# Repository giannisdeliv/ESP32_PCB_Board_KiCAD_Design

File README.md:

# ESP32-C3 Sensor Board

It has been designed in KiCad as part of the Udemy course *Advanced PCB Design with KiCad 9*.(udemy.com/course/advanced-pcb-design-with-kicad/)

The design follows the course. 
I did the schematic capture, layout, and fabrication outputs.

## Features

- **MCU:** ESP32-C3-WROOM-02 (Wi-Fi / BLE), external 32 Mbit SPI flash (W25Q32JV)
- **USB:** USB-C, CP2102N USB-UART bridge, USBLC6-2SC6 ESD protection, resettable fuse
- **Power:** MCP73871 Li-Po charger with power-path management, LM1117 3.3 V LDO, JST-PH battery connector
- **Sensors:** BME280 (temperature / humidity / pressure), TEMT6000 ambient light, electret microphone with MAX4466 amplifier
- **Storage / UI:** microSD slot, status LEDs, Boot and Reset buttons
- **Debug:** test points on the SPI bus, pin headers for expansion

The custom footprint library "ESP32_Project_Footprints" and its 3D models were provided by the course and are not redistributed here. 
The footprints are embedded in "Demo.kicad_pcb", so the layout opens. 
Updating the PCB from the schematic requires the original library.

(Design only, not fabricated or tested.)

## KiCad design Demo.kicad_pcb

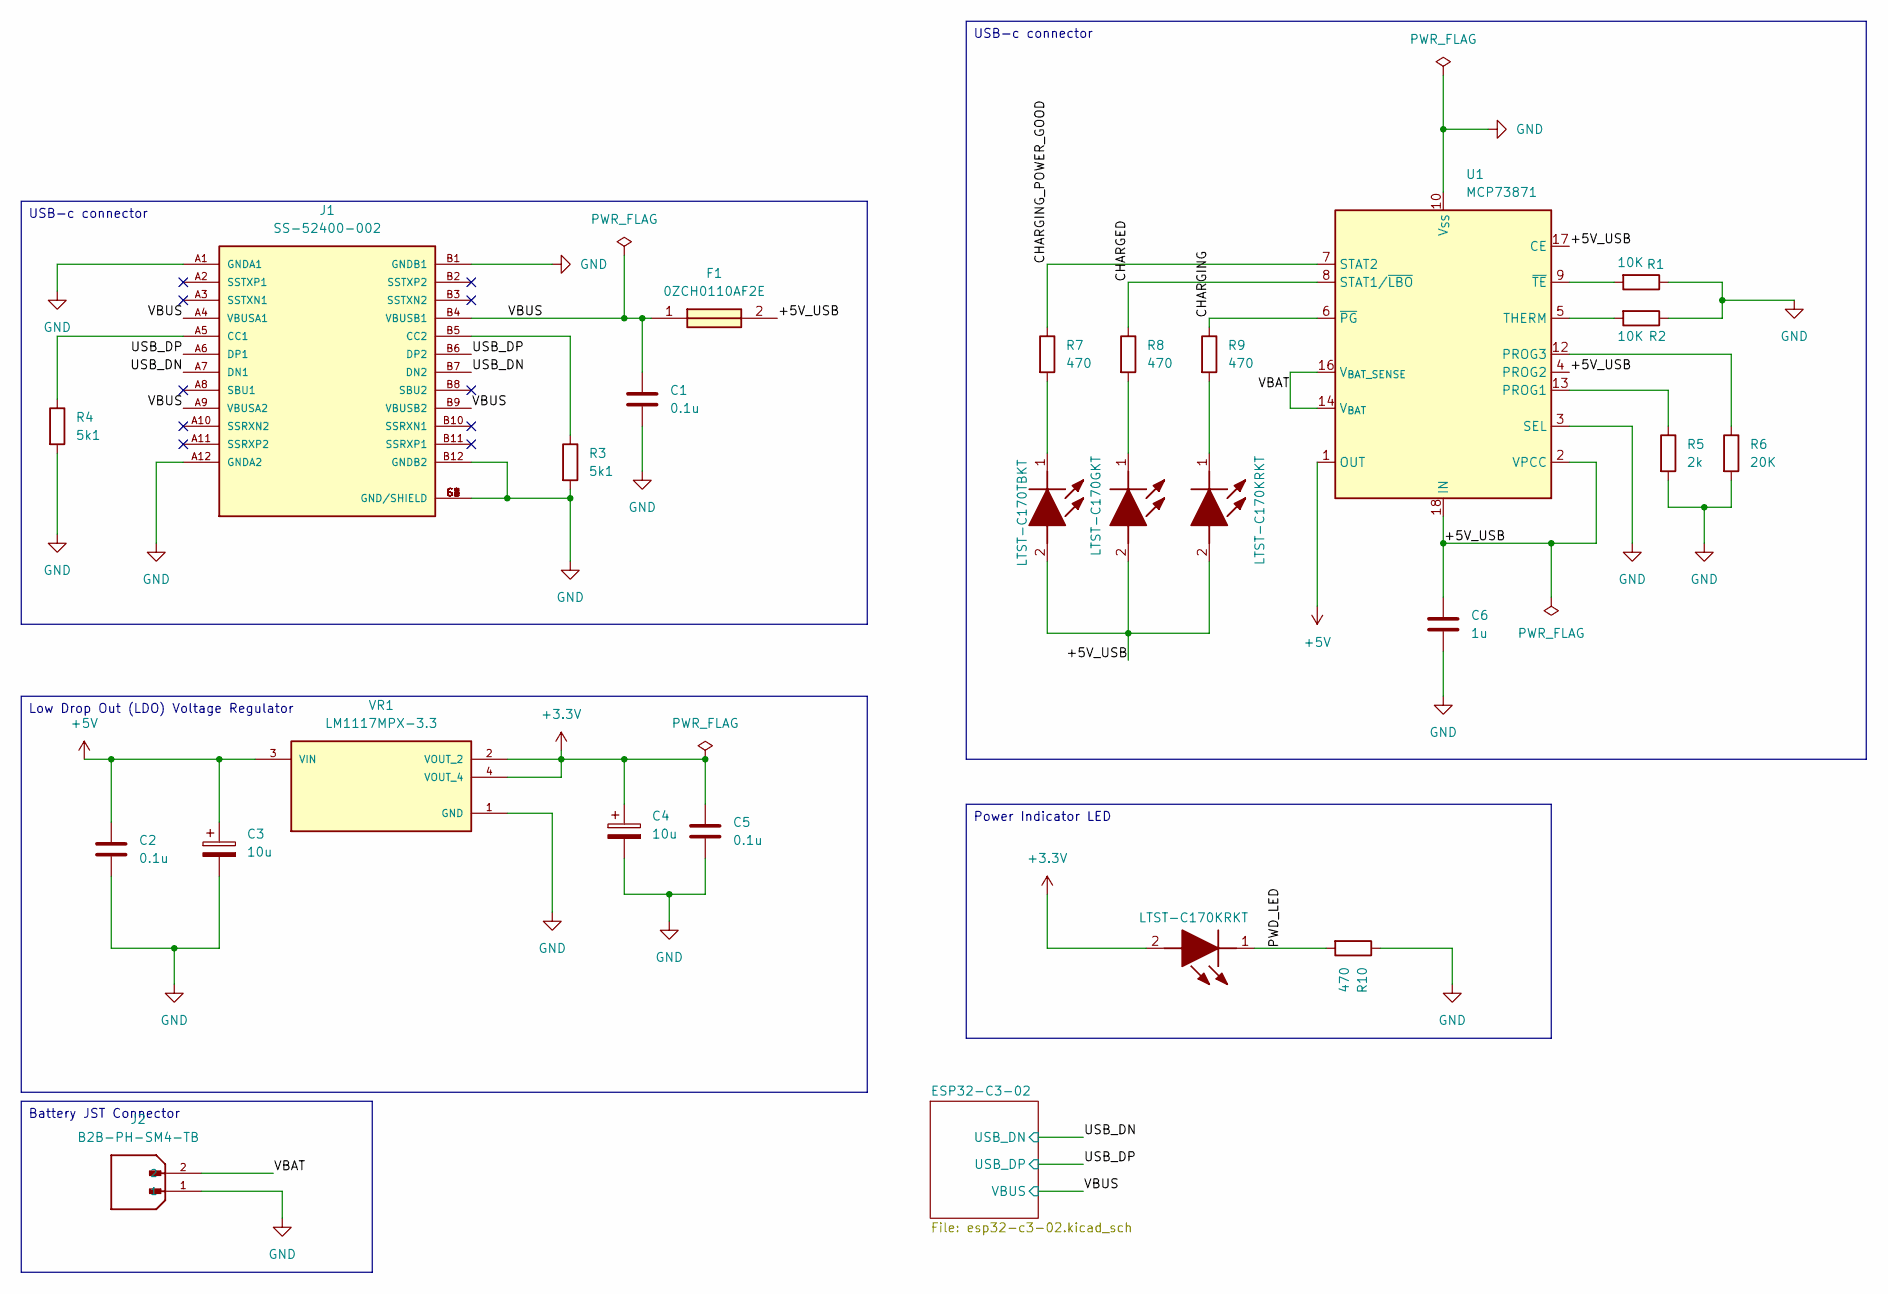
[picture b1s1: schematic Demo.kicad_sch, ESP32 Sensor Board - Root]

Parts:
C1, C2, C5: 0.1u; C_0805_2012Metric
C3, C4: 10u; T491A
C6: 1u; C_0805_2012Metric
F1: 0ZCH0110AF2E; FUSC3226X100N; Manufacturer_Part_Number 0ZCH0110AF2E
J1: SS-52400-002; BELFUSE_SS-52400-002; PARTREV A0
J2: B2B-PH-SM4-TB; JST_B2B-PH-SM4-TB; PARTREV N/A
LED1, LED4: LTST-C170KRKT; LEDC2012X120N; Manufacturer_Part_Number LTST-C170KRKT; Mouser Part Number 859-LTST-C170KRKT
LED2: LTST-C170GKT; LEDC2012X120N; Manufacturer_Part_Number LTST-C170GKT; Mouser Part Number 859-LTST-C170GKT
LED3: LTST-C170TBKT; LEDC2012X120N; Manufacturer_Part_Number LTST-C170TBKT; Mouser Part Number 859-LTST-C170TBKT
R1, R2: 10K; R_0805_2012Metric
R3, R4: 5k1; R_0805_2012Metric
R5: 2k; R_0805_2012Metric
R6: 20K; R_0805_2012Metric
R7, R8, R9, R10: 470; R_0805_2012Metric
U1: MCP73871; QFN-20-1EP_4x4mm_P0.5mm_EP2.5x2.5mm
VR1: LM1117MPX-3.3; VREG_LM1117MPX-3.3

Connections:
+3.3V: C4.1, C5.1, LED4.2 (A), VR1.2 (VOUT_2), VR1.4 (VOUT_4); also elsewhere on the board
+5V: C2.1, C3.1, U1.1 (OUT), U1.20 (OUT), VR1.3 (VIN)
/+5V_USB: C6.1, F1.2, LED1.2 (A), LED2.2 (A), LED3.2 (A), U1.2 (VPCC), U1.4 (PROG2), U1.17 (CE), U1.18 (IN), U1.19 (IN)
/CHARGED: R8.1, U1.8 (STAT1/~LBO)
/CHARGING: R9.1, U1.6 (~PG)
/CHARGING_POWER_GOOD: R7.1, U1.7 (STAT2)
/PWD_LED: LED4.1 (K), R10.2
/USB_DN: J1.A7 (DN1), J1.B7 (DN2); also elsewhere on the board
/USB_DP: J1.A6 (DP1), J1.B6 (DP2); also elsewhere on the board
/VBAT: J2.2, U1.14 (V_{BAT}), U1.15 (V_{BAT}), U1.16 (V_{BAT_SENSE})
/VBUS: C1.1, F1.1, J1.A4 (VBUSA1), J1.A9 (VBUSA2), J1.B4 (VBUSB1), J1.B9 (VBUSB2); also elsewhere on the board
GND: C1.2, C2.2, C3.2, C4.2, C5.2, C6.2, J1.A1 (GNDA1), J1.A12 (GNDA2), J1.B1 (GNDB1), J1.B12 (GNDB2), J1.G1 (GND/SHIELD), J1.G2 (GND/SHIELD), J1.G3 (GND/SHIELD), J1.G4 (GND/SHIELD), J1.S1 (GND/SHIELD), J1.S2 (GND/SHIELD), J1.S3 (GND/SHIELD), J1.S4 (GND/SHIELD), J2.1, R1.1, R2.1, R3.2, R4.2, R5.2, R6.2, R10.1, U1.3 (SEL), U1.10 (V_{SS}), U1.11 (V_{SS}), U1.21 (V_{SS}), VR1.1 (GND); also elsewhere on the board
unnamed: J1.A5 (CC1), R4.1
unnamed: J1.B5 (CC2), R3.1
unnamed: LED1.1 (K), R9.2
unnamed: LED2.1 (K), R8.2
unnamed: LED3.1 (K), R7.2
unnamed: R5.1, U1.13 (PROG1)
unnamed: R6.1, U1.12 (PROG3)
unnamed: R2.2, U1.5 (THERM)
unnamed: R1.2, U1.9 (~TE)

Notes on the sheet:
USB-c connector
Power Indicator LED
Low Drop Out (LDO) Voltage Regulator
Battery JST Connector

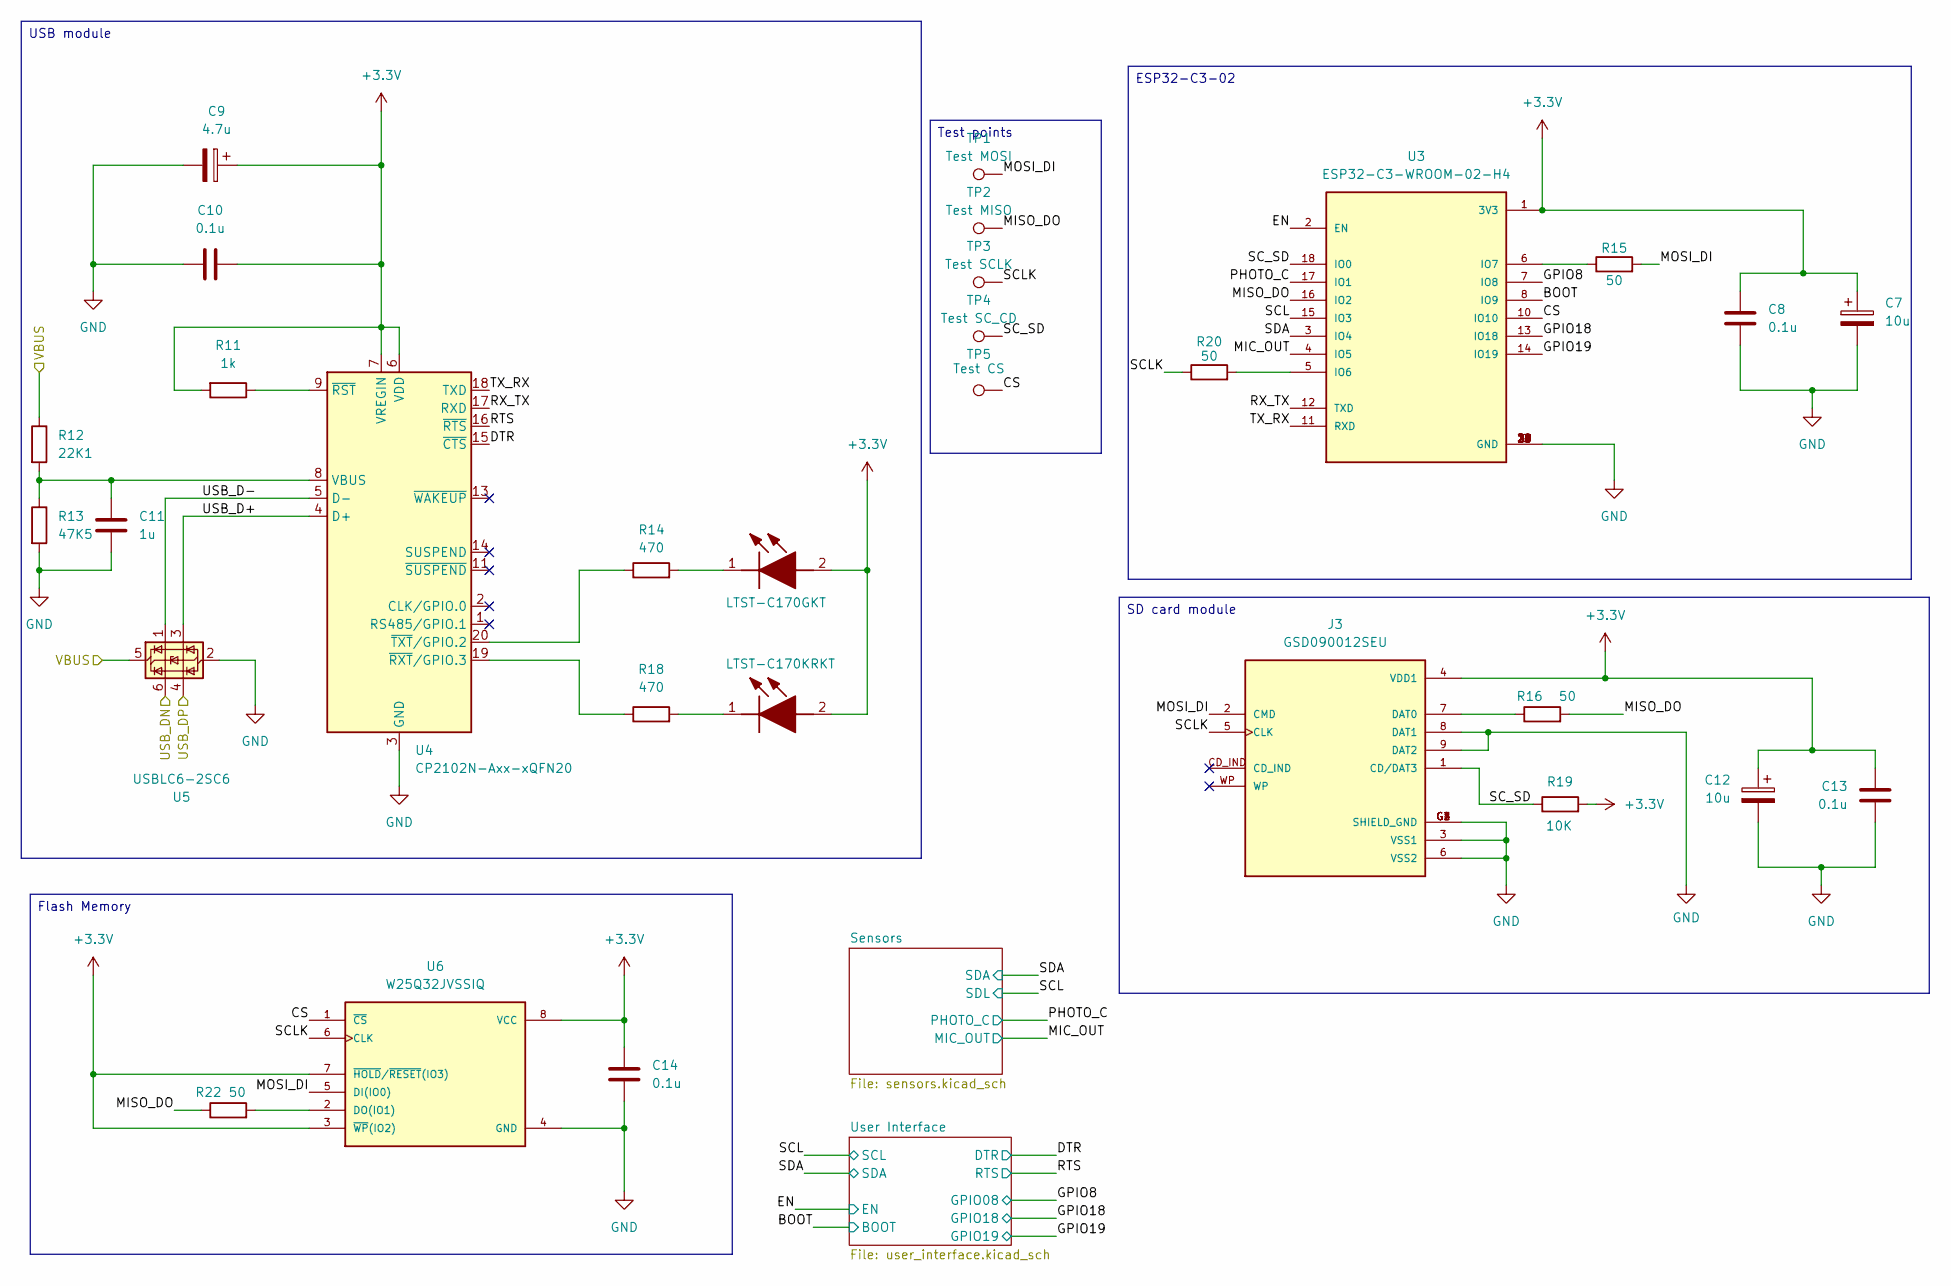
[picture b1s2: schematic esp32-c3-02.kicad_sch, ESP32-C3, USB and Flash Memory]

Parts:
C7, C12: 10u; T491A
C8, C10, C13, C14: 0.1u; C_0805_2012Metric
C9: 4.7u; T491A
C11: 1u; C_0805_2012Metric
J3: GSD090012SEU; AMPHENOL_GSD090012SEU; PARTREV E
LED5: LTST-C170GKT; LEDC2012X120N; Manufacturer_Part_Number LTST-C170GKT; Mouser Part Number 859-LTST-C170GKT
LED6: LTST-C170KRKT; LEDC2012X120N; Manufacturer_Part_Number LTST-C170KRKT; Mouser Part Number 859-LTST-C170KRKT
R11: 1k; R_0805_2012Metric
R12: 22K1; R_0805_2012Metric
R13: 47K5; R_0805_2012Metric
R14, R18: 470; R_0805_2012Metric
R15, R16, R20, R22: 50; R_0805_2012Metric
R19: 10K; R_0805_2012Metric
TP1: Test MOSI; TestPoint_Pad_D1.0mm
TP2: Test MISO; TestPoint_Pad_D1.0mm
TP3: Test SCLK; TestPoint_Pad_D1.0mm
TP4: Test SC_CD; TestPoint_Pad_D1.0mm
TP5: Test CS; TestPoint_Pad_D1.0mm
U3: ESP32-C3-WROOM-02-H4; MODULE_ESP32-C3-WROOM-02-H4
U4: CP2102N-Axx-xQFN20; SiliconLabs_QFN-20-1EP_3x3mm_P0.5mm_EP1.8x1.8mm
U5: USBLC6-2SC6; SOT-23-6
U6: W25Q32JVSSIQ; SOIC127P790X216-8N; M_PART_NUMBER W25QXX

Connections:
+3.3V: C7.1, C8.1, C9.1, C10.1, C12.1, C13.1, C14.1, J3.4 (VDD1), LED5.2 (A), LED6.2 (A), R11.2, R19.2, U3.1 (3V3), U4.6 (VDD), U4.7 (VREGIN), U6.3 (~WP(IO2)), U6.7 (~HOLD/~RESET(IO3)), U6.8 (VCC); also elsewhere on the board
/ESP32-C3-02/BOOT: U3.8 (IO9); also elsewhere on the board
/ESP32-C3-02/CS: TP5.1 (1_1), U3.10 (IO10), U6.1 (~CS)
/ESP32-C3-02/DTR: U4.15 (~CTS); also elsewhere on the board
/ESP32-C3-02/EN: U3.2 (EN); also elsewhere on the board
/ESP32-C3-02/GPIO8: U3.7 (IO8); also elsewhere on the board
/ESP32-C3-02/GPIO18: U3.13 (IO18); also elsewhere on the board
/ESP32-C3-02/GPIO19: U3.14 (IO19); also elsewhere on the board
/ESP32-C3-02/MIC_OUT: U3.4 (IO5); also elsewhere on the board
/ESP32-C3-02/MISO_DO: R16.2, R22.1, TP2.1 (1_1), U3.16 (IO2)
/ESP32-C3-02/MOSI_DI: J3.2 (CMD), R15.2, TP1.1 (1_1), U6.5 (DI(IO0))
/ESP32-C3-02/PHOTO_C: U3.17 (IO1); also elsewhere on the board
/ESP32-C3-02/RTS: U4.16 (~RTS); also elsewhere on the board
/ESP32-C3-02/RX_TX: U3.12 (TXD), U4.17 (RXD)
/ESP32-C3-02/SCL: U3.15 (IO3); also elsewhere on the board
/ESP32-C3-02/SCLK: J3.5 (CLK), R20.1, TP3.1 (1_1), U6.6 (CLK)
/ESP32-C3-02/SC_SD: J3.1 (CD/DAT3), R19.1, TP4.1 (1_1), U3.18 (IO0)
/ESP32-C3-02/SDA: U3.3 (IO4); also elsewhere on the board
/ESP32-C3-02/TX_RX: U3.11 (RXD), U4.18 (TXD)
/ESP32-C3-02/USB_D+: U4.4 (D+), U5.3 (I/O2)
/ESP32-C3-02/USB_D-: U4.5 (D-), U5.1 (I/O1)
/USB_DN: U5.6 (I/O1); also elsewhere on the board
/USB_DP: U5.4 (I/O2); also elsewhere on the board
/VBUS: R12.1, U5.5 (VBUS); also elsewhere on the board
GND: C7.2, C8.2, C9.2, C10.2, C11.2, C12.2, C13.2, C14.2, J3.3 (VSS1), J3.6 (VSS2), J3.8 (DAT1), J3.9 (DAT2), J3.G1 (SHIELD_GND), J3.G2 (SHIELD_GND), J3.G3 (SHIELD_GND), J3.G4 (SHIELD_GND), R13.2, U3.9 (GND), U3.19 (GND), U3.20 (GND), U3.21 (GND), U3.22 (GND), U3.23 (GND), U3.24 (GND), U3.25 (GND), U3.26 (GND), U3.27 (GND), U3.28 (GND), U3.29 (GND), U3.30 (GND), U3.31 (GND), U3.32 (GND), U3.33 (GND), U3.34 (GND), U3.35 (GND), U3.36 (GND), U3.37 (GND), U3.38 (GND), U3.39 (GND), U4.3 (GND), U4.12 (GND), U4.21 (GND), U5.2 (GND), U6.4 (GND); also elsewhere on the board
unnamed: J3.7 (DAT0), R16.1
unnamed: LED5.1 (K), R14.2
unnamed: LED6.1 (K), R18.2
unnamed: R20.2, U3.5 (IO6)
unnamed: R15.1, U3.6 (IO7)
unnamed: C11.1, R12.2, R13.1, U4.8 (VBUS)
unnamed: R11.1, U4.9 (~RST)
unnamed: R18.1, U4.19 (~RXT/GPIO.3)
unnamed: R14.1, U4.20 (~TXT/GPIO.2)
unnamed: R22.2, U6.2 (DO(IO1))

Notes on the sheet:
Flash Memory
USB module
ESP32-C3-02
SD card module
Test points

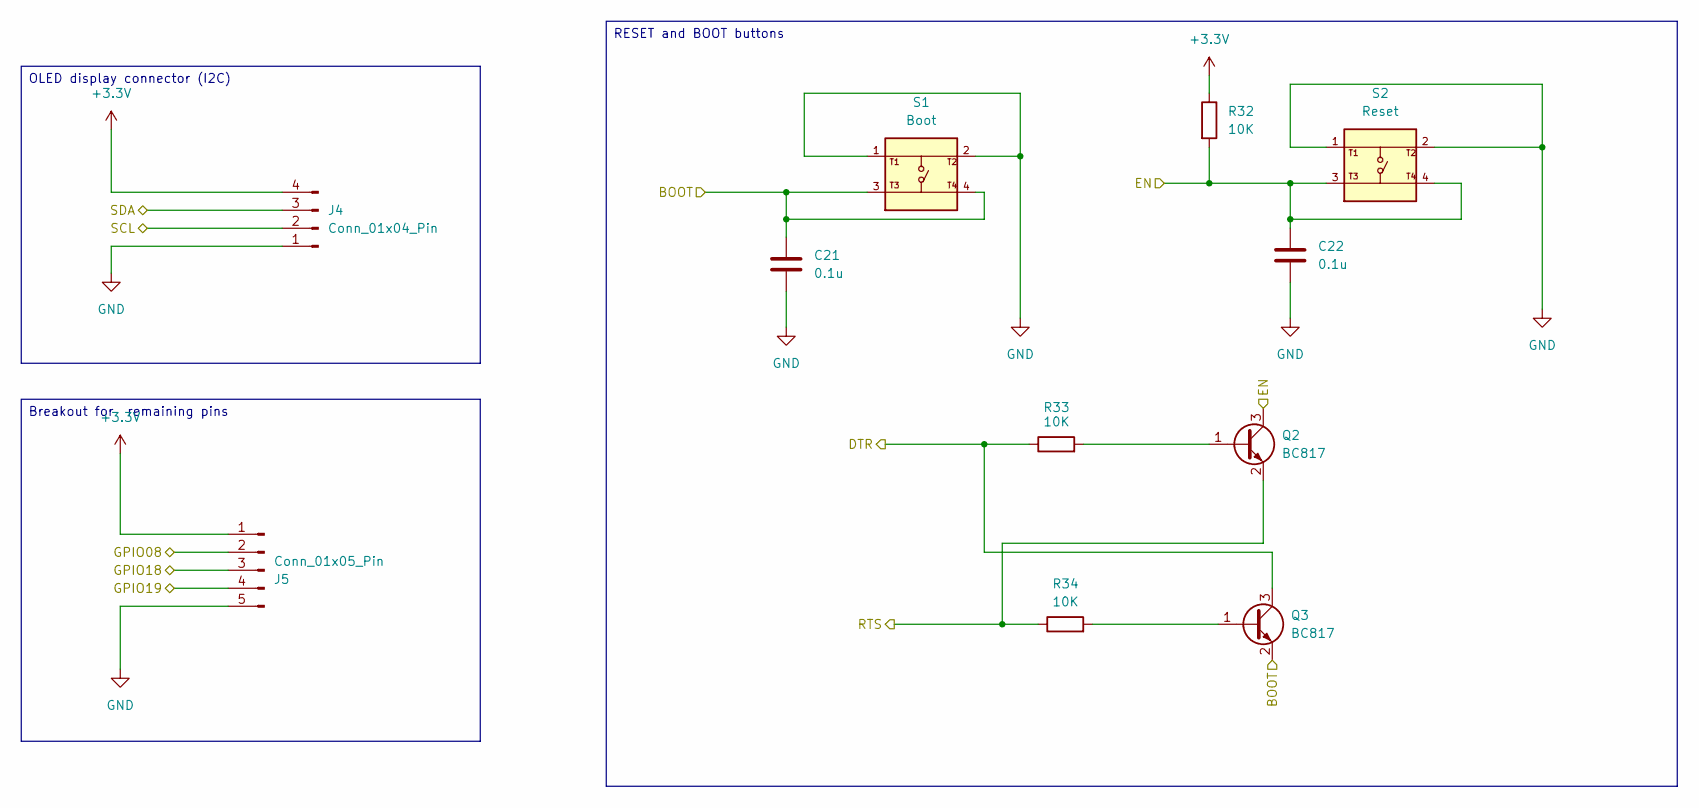
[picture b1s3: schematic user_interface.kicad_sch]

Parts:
C21, C22: 0.1u; C_0805_2012Metric
J4: Conn_01x04_Pin; PinHeader_1x04_P2.54mm_Vertical
J5: Conn_01x05_Pin; PinHeader_1x05_P2.54mm_Vertical
Q2, Q3: BC817; SOT-23
R32, R33, R34: 10K; R_0805_2012Metric
S1: Boot; SW_USLPT2819DT2TR; PARTREV P
S2: Reset; SW_USLPT2819DT2TR; PARTREV P

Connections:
+3.3V: J4.4, J5.1, R32.1; also elsewhere on the board
/ESP32-C3-02/BOOT: C21.1, Q3.2 (E), S1.3, S1.4; also elsewhere on the board
/ESP32-C3-02/DTR: Q3.3 (C), R33.1; also elsewhere on the board
/ESP32-C3-02/EN: C22.1, Q2.3 (C), R32.2, S2.3, S2.4; also elsewhere on the board
/ESP32-C3-02/GPIO8: J5.2; also elsewhere on the board
/ESP32-C3-02/GPIO18: J5.3; also elsewhere on the board
/ESP32-C3-02/GPIO19: J5.4; also elsewhere on the board
/ESP32-C3-02/RTS: Q2.2 (E), R34.1; also elsewhere on the board
/ESP32-C3-02/SCL: J4.2; also elsewhere on the board
/ESP32-C3-02/SDA: J4.3; also elsewhere on the board
GND: C21.2, C22.2, J4.1, J5.5, S1.1, S1.2, S2.1, S2.2; also elsewhere on the board
unnamed: Q2.1 (B), R33.2
unnamed: Q3.1 (B), R34.2

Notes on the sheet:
RESET and BOOT buttons
Breakout for remaining pins
OLED display connector (I2C)

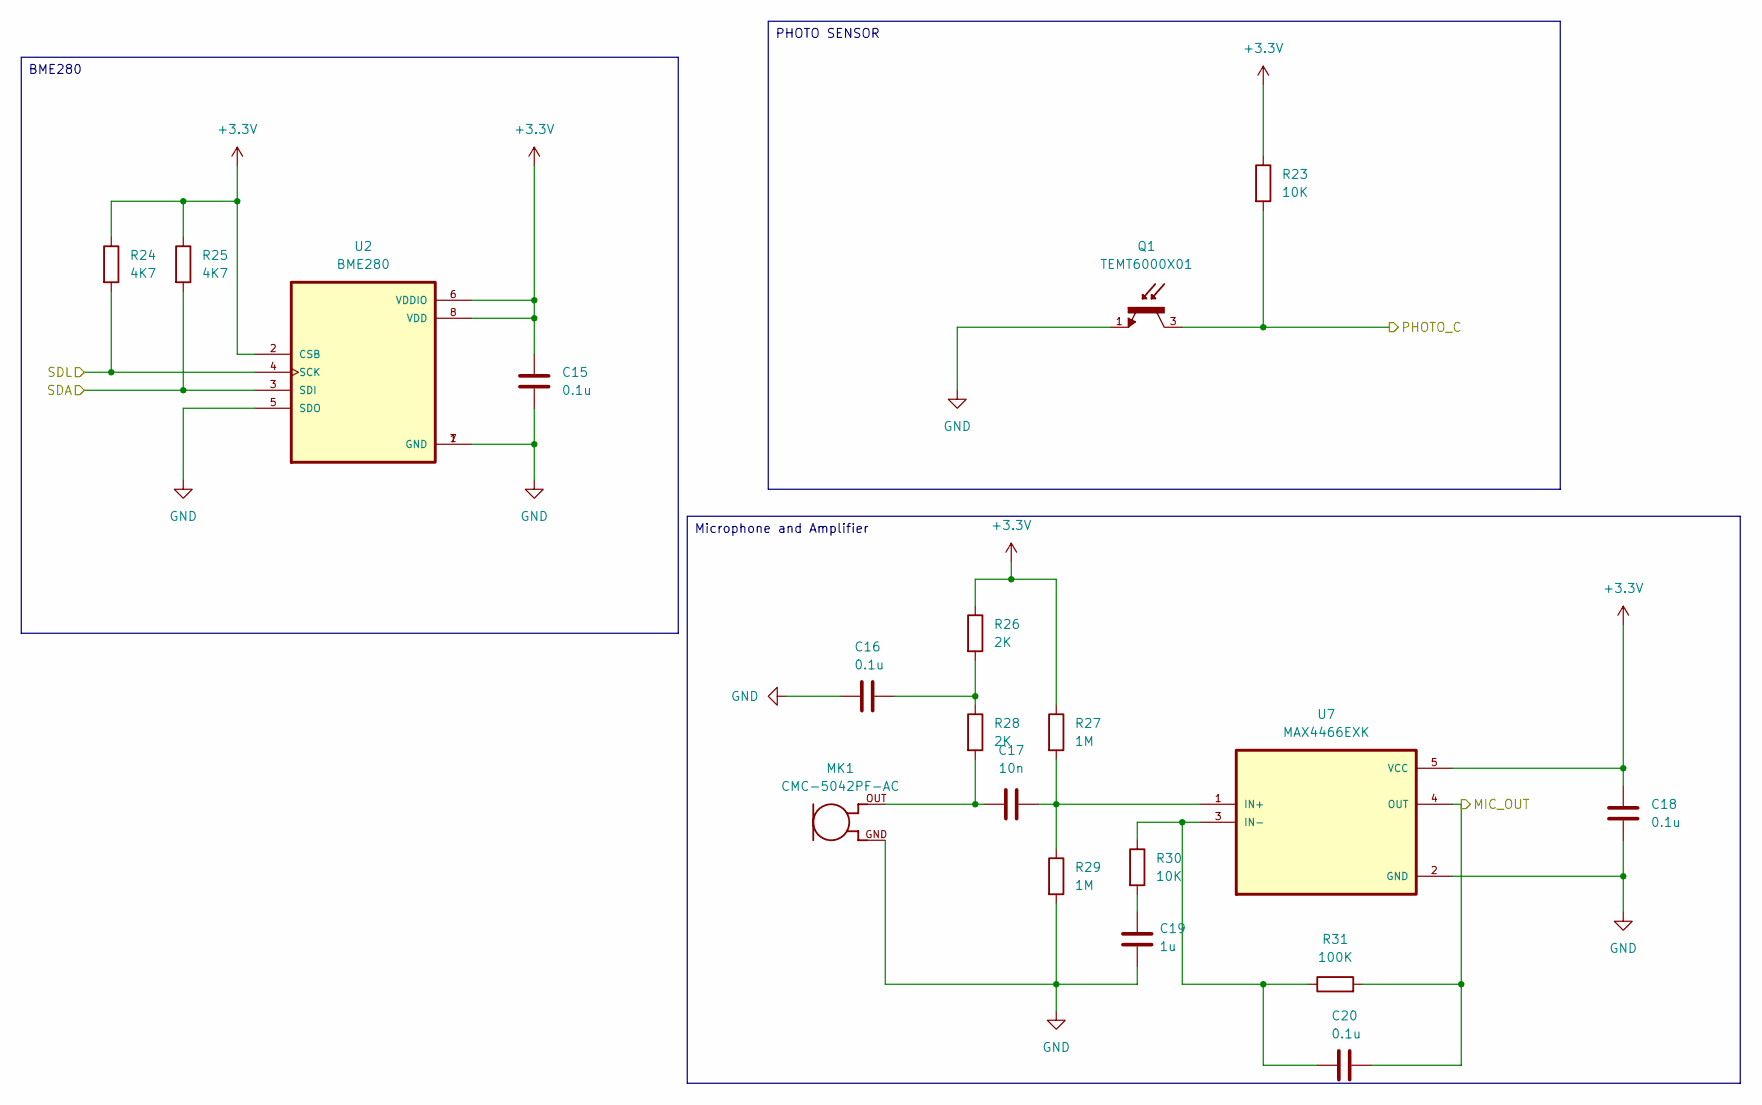
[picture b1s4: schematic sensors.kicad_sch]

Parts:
C15, C16, C18, C20: 0.1u; C_0805_2012Metric
C17: 10n; C_0805_2012Metric
C19: 1u; C_0805_2012Metric
MK1: CMC-5042PF-AC; CUI_CMC-5042PF-AC
Q1: TEMT6000X01; TRANS_TEMT6000X01; PARTREV 1.9
R23, R30: 10K; R_0805_2012Metric
R24, R25: 4K7; R_0805_2012Metric
R26, R28: 2K; R_0805_2012Metric
R27, R29: 1M; R_0805_2012Metric
R31: 100K; R_0805_2012Metric
U2: BME280; PSON65P250X250X100-8N
U7: MAX4466EXK; SOT65P210X110-5N

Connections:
+3.3V: C15.1, C18.1, R23.1, R24.1, R25.1, R26.1, R27.1, U2.2 (CSB), U2.6 (VDDIO), U2.8 (VDD), U7.5 (VCC); also elsewhere on the board
/ESP32-C3-02/MIC_OUT: C20.2, R31.2, U7.4 (OUT); also elsewhere on the board
/ESP32-C3-02/PHOTO_C: Q1.3, R23.2; also elsewhere on the board
/ESP32-C3-02/SCL: R24.2, U2.4 (SCK); also elsewhere on the board
/ESP32-C3-02/SDA: R25.2, U2.3 (SDI); also elsewhere on the board
GND: C15.2, C16.1, C18.2, C19.2, MK1.GND, Q1.1, R29.2, U2.1 (GND), U2.5 (SDO), U2.7 (GND), U7.2 (GND); also elsewhere on the board
unnamed: C16.2, R26.2, R28.1
unnamed: C17.1, MK1.OUT, R28.2
unnamed: C19.1, R30.2
unnamed: C17.2, R27.2, R29.1, U7.1 (IN+)
unnamed: C20.1, R30.1, R31.1, U7.3 (IN-)

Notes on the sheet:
BME280
PHOTO SENSOR
Microphone and Amplifier

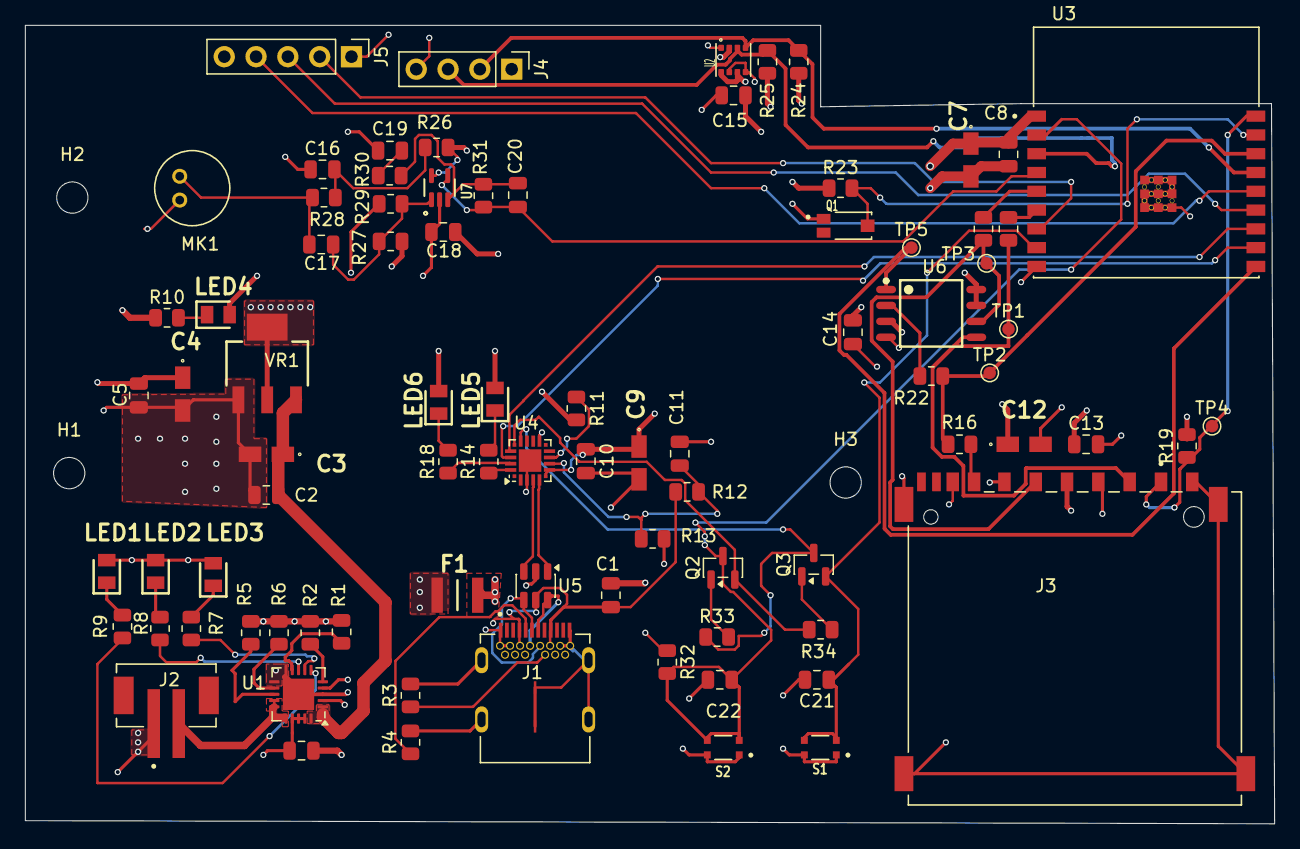
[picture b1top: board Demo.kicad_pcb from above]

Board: 4 copper layers, 99.8 x 63.8 mm, 88 parts (0 on the bottom side), 58 nets.

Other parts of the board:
Η1, Η2, Η3: MountingHole_2.5mm

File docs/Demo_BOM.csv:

"Reference","Qty","Value","DNP","Exclude from BOM","Exclude from Board","Exclude from Simulation","Exclude from Position Files","Footprint","Datasheet"
"C1,C2,C5,C8,C10,C13,C14,C15,C16,C18,C20,C21,C22","13","0.1u","","","","","${EXCLUDE_FROM_POS_FILES}","Capacitor_SMD:C_0805_2012Metric",""
"C3,C4,C7,C12","4","10u","","","","","${EXCLUDE_FROM_POS_FILES}","ESP32_Project_Footprints:T491A",""
"C6,C11,C19","3","1u","","","","","${EXCLUDE_FROM_POS_FILES}","Capacitor_SMD:C_0805_2012Metric",""
"C9","1","4.7u","","","","","${EXCLUDE_FROM_POS_FILES}","ESP32_Project_Footprints:T491A",""
"C17","1","10n","","","","","${EXCLUDE_FROM_POS_FILES}","Capacitor_SMD:C_0805_2012Metric",""
"F1","1","0ZCH0110AF2E","","","","","${EXCLUDE_FROM_POS_FILES}","ESP32_Project_Footprints:FUSC3226X100N","https://www.belfuse.com/resources/datasheets/circuitprotecti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"
"J1","1","SS-52400-002","","","","","${EXCLUDE_FROM_POS_FILES}","ESP32_Project_Footprints:BELFUSE_SS-52400-002",""
"J2","1","B2B-PH-SM4-TB","","","","","${EXCLUDE_FROM_POS_FILES}","ESP32_Project_Footprints:JST_B2B-PH-SM4-TB",""
"J3","1","GSD090012SEU","","","","","${EXCLUDE_FROM_POS_FILES}","ESP32_Project_Footprints:AMPHENOL_GSD090012SEU",""
"J4","1","Conn_01x04_Pin","","","","","${EXCLUDE_FROM_POS_FILES}","Connector_PinHeader_2.54mm:PinHeader_1x04_P2.54mm_Vertical",""
"J5","1","Conn_01x05_Pin","","","","","${EXCLUDE_FROM_POS_FILES}","Connector_PinHeader_2.54mm:PinHeader_1x05_P2.54mm_Vertical",""
"LED1,LED4,LED6","3","LTST-C170KRKT","","","","","${EXCLUDE_FROM_POS_FILES}","ESP32_Project_Footprints:LEDC2012X120N","https://componentsearchengine.com/Datasheets/1/LTST-C170KRKT.pdf"
"LED2,LED5","2","LTST-C170GKT","","","","","${EXCLUDE_FROM_POS_FILES}","ESP32_Project_Footprints:LEDC2012X120N","https://mm.digikey.com/Volume0/opasdata/d220001/medias/docus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"
"LED3","1","LTST-C170TBKT","","","","","${EXCLUDE_FROM_POS_FILES}","ESP32_Project_Footprints:LEDC2012X120N","https://componentsearchengine.com/Datasheets/1/LTST-C170TBKT.pdf"
"MK1","1","CMC-5042PF-AC","","","","","${EXCLUDE_FROM_POS_FILES}","ESP32_Project_Footprints:CUI_CMC-5042PF-AC",""
"Q1","1","TEMT6000X01","","","","","${EXCLUDE_FROM_POS_FILES}","ESP32_Project_Footprints:TRANS_TEMT6000X01",""
"Q2,Q3","2","BC817","","","","","${EXCLUDE_FROM_POS_FILES}","Package_TO_SOT_SMD:SOT-23","https://www.onsemi.com/pub/Collateral/BC818-D.pdf"
"R1,R2,R19,R23,R30,R32,R33,R34","8","10K","","","","","${EXCLUDE_FROM_POS_FILES}","Resistor_SMD:R_0805_2012Metric",""
"R3,R4","2","5k1","","","","","${EXCLUDE_FROM_POS_FILES}","Resistor_SMD:R_0805_2012Metric",""
"R5","1","2k","","","","","${EXCLUDE_FROM_POS_FILES}","Resistor_SMD:R_0805_2012Metric",""
"R6","1","20K","","","","","${EXCLUDE_FROM_POS_FILES}","Resistor_SMD:R_0805_2012Metric",""
"R7,R8,R9,R10,R14,R18","6","470","","","","","${EXCLUDE_FROM_POS_FILES}","Resistor_SMD:R_0805_2012Metric",""
"R11","1","1k","","","","","${EXCLUDE_FROM_POS_FILES}","Resistor_SMD:R_0805_2012Metric",""
"R12","1","22K1","","","","","${EXCLUDE_FROM_POS_FILES}","Resistor_SMD:R_0805_2012Metric",""
"R13","1","47K5","","","","","${EXCLUDE_FROM_POS_FILES}","Resistor_SMD:R_0805_2012Metric",""
"R15,R16,R20,R22","4","50","","","","","${EXCLUDE_FROM_POS_FILES}","Resistor_SMD:R_0805_2012Metric",""
"R24,R25","2","4K7","","","","","${EXCLUDE_FROM_POS_FILES}","Resistor_SMD:R_0805_2012Metric",""
"R26,R28","2","2K","","","","","${EXCLUDE_FROM_POS_FILES}","Resistor_SMD:R_0805_2012Metric",""
"R27,R29","2","1M","","","","","${EXCLUDE_FROM_POS_FILES}","Resistor_SMD:R_0805_2012Metric",""
"R31","1","100K","","","","","${EXCLUDE_FROM_POS_FILES}","Resistor_SMD:R_0805_2012Metric",""
"S1","1","Boot","","","","","${EXCLUDE_FROM_POS_FILES}","ESP32_Project_Footprints:SW_USLPT2819DT2TR",""
"S2","1","Reset","","","","","${EXCLUDE_FROM_POS_FILES}","ESP32_Project_Footprints:SW_USLPT2819DT2TR",""
"TP1","1","Test MOSI","","","","","${EXCLUDE_FROM_POS_FILES}","TestPoint:TestPoint_Pad_D1.0mm",""
"TP2","1","Test MISO","","","","","${EXCLUDE_FROM_POS_FILES}","TestPoint:TestPoint_Pad_D1.0mm",""
"TP3","1","Test SCLK","","","","","${EXCLUDE_FROM_POS_FILES}","TestPoint:TestPoint_Pad_D1.0mm",""
"TP4","1","Test SC_CD","","","","","${EXCLUDE_FROM_POS_FILES}","TestPoint:TestPoint_Pad_D1.0mm",""
"TP5","1","Test CS","","","","","${EXCLUDE_FROM_POS_FILES}","TestPoint:TestPoint_Pad_D1.0mm",""
"U1","1","MCP73871","","","","","${EXCLUDE_FROM_POS_FILES}","Package_DFN_QFN:QFN-20-1EP_4x4mm_P0.5mm_EP2.5x2.5mm","http://www.mouser.com/ds/2/268/22090a-52174.pdf"
"U2","1","BME280","","","","","${EXCLUDE_FROM_POS_FILES}","ESP32_Project_Footprints:PSON65P250X250X100-8N",""
"U3","1","ESP32-C3-WROOM-02-H4","","","","","${EXCLUDE_FROM_POS_FILES}","ESP32_Project_Footprints:MODULE_ESP32-C3-WROOM-02-H4",""
"U4","1","CP2102N-Axx-xQFN20","","","","","${EXCLUDE_FROM_POS_FILES}","Package_DFN_QFN:SiliconLabs_QFN-20-1EP_3x3mm_P0.5mm_EP1.8x1.8mm","https://www.silabs.com/documents/public/data-sheets/cp2102n-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"
"U5","1","USBLC6-2SC6","","","","","${EXCLUDE_FROM_POS_FILES}","Package_TO_SOT_SMD:SOT-23-6","https://www.st.com/resource/en/datasheet/usblc6-2.pdf"
"U6","1","W25Q32JVSSIQ","","","","","${EXCLUDE_FROM_POS_FILES}","ESP32_Project_Footprints:SOIC127P790X216-8N",""
"U7","1","MAX4466EXK","","","","","${EXCLUDE_FROM_POS_FILES}","ESP32_Project_Footprints:SOT65P210X110-5N",""
"VR1","1","LM1117MPX-3.3","","","","","${EXCLUDE_FROM_POS_FILES}","ESP32_Project_Footprints:VREG_LM1117MPX-3.3",""
